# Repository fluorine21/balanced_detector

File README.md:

# balanced_detector
A balanced amplifier used to create a balanced photodetector out of two seperate photodetectors.

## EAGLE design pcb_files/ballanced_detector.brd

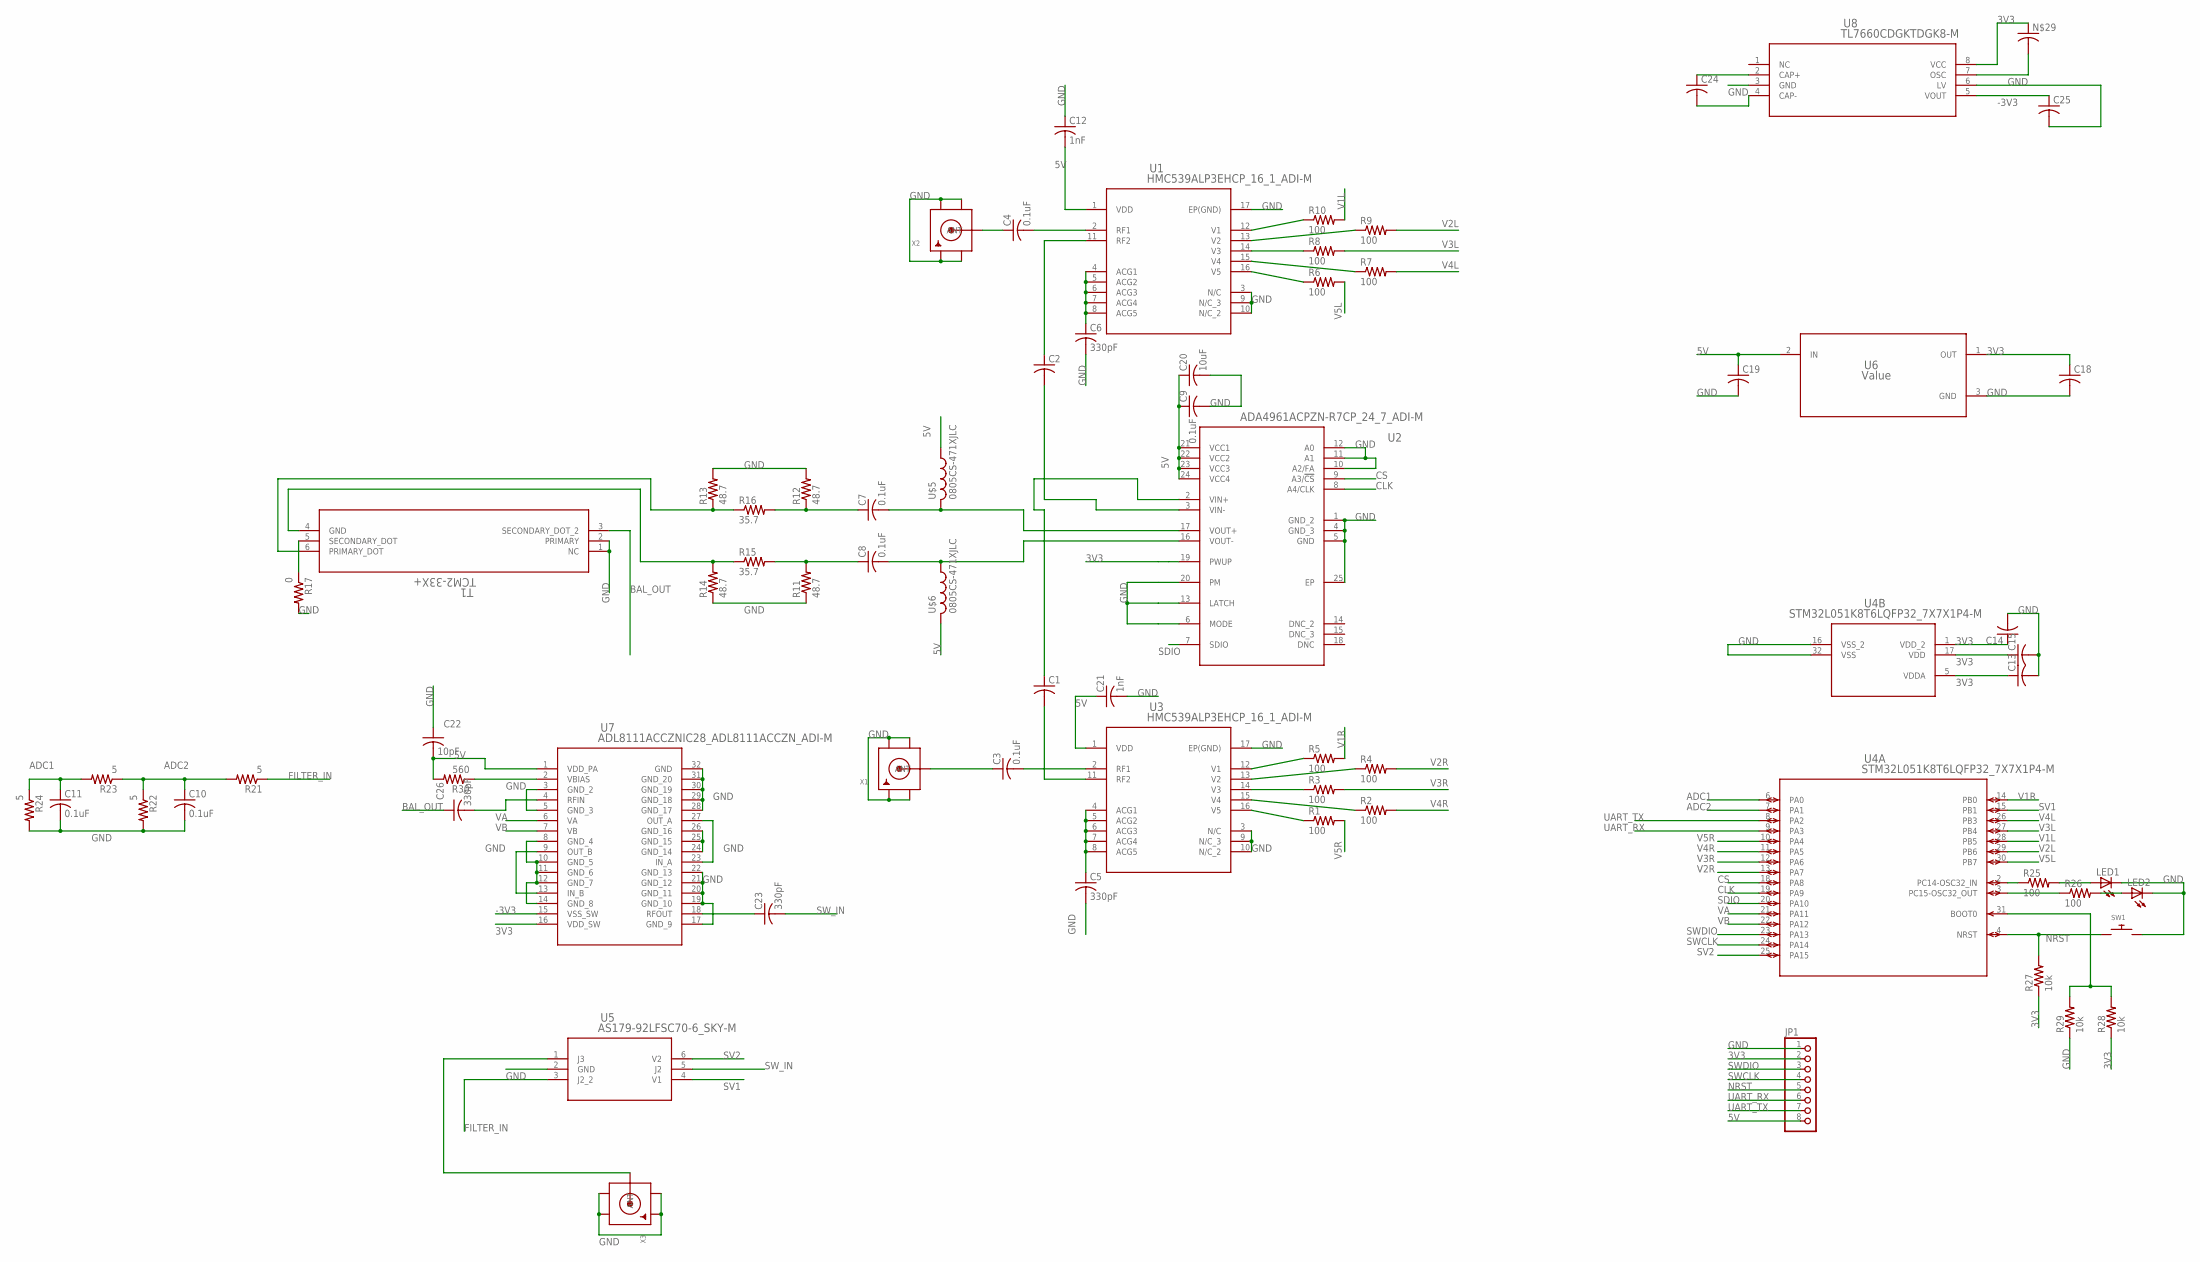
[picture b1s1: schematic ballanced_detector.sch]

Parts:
C1, C2, C13, C14, C15, C18, C19: C-USC0402; C0402
C3, C4, C7, C8, C9, C10, C11: 0.1uF; C0402
C5, C6, C23, C26: 330pF; C0402
C12, C21: 1nF; C0402
C20: 10uF; C0402
C22: 10pF; C0402
C24, C25: C-USC1210; C1210
JP1: PINHD-1X8CLEANBIG; 1X08-CLEANBIG
LED1, LED2: LEDCHIP-LED0805; CHIP-LED0805
N$29: C-USC1210; C1210
R1, R2, R3, R4, R5, R6, R7, R8, R9, R10, R25, R26: 100; R0402
R11, R12, R13, R14: 48.7; R0402
R15, R16: 35.7; R0402
R17: 0; R0402
R21, R22, R23, R24: 5; R0402
R27, R28, R29: 10k; R0402
R30: 560; R0402
SW1: SWITCH_PUSHBUTTONC&K_KSS; BTN_CK_KSS
T1: TCM2-33X+; DB1627_MNC
U1, U3: HMC539ALP3EHCP_16_1_ADI-M; HCP_16_1_ADI-M
U2: ADA4961ACPZN-R7CP_24_7_ADI-M; CP_24_7_ADI-M
U4: STM32L051K8T6LQFP32_7X7X1P4-M; LQFP32_7X7X1P4-M
U5: AS179-92LFSC70-6_SKY-M; SC70-6_SKY-M
U6: Value; DBZ0003A_N
U7: ADL8111ACCZNIC28_ADL8111ACCZN_ADI-M; IC28_ADL8111ACCZN_ADI-M
U8: TL7660CDGKTDGK8-M; DGK8-M
U$5, U$6: 0805CS-471XJLC; R0805
X1, X2, X3: SMACONNECTOR_EDGE; SMA_EDGELAUNCH

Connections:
3V3: C13.1, C14.1, C15.1, C18.1, JP1.2, N$29.1, R27.1, R28.1, U2.19 (PWUP), U4.1 (VDD_2), U4.5 (VDDA), U4.17 (VDD), U6.1 (OUT), U7.16 (VDD_SW), U8.8 (VCC)
5V: C9.1, C12.2, C19.1, C20.1, C21.1, C22.2, JP1.8, R30.2, U1.1 (VDD), U2.21 (VCC1), U2.22 (VCC2), U2.23 (VCC3), U2.24 (VCC4), U3.1 (VDD), U6.2 (IN), U7.1 (VDD_PA), U$5.1, U$6.2
-3V3: C25.1, U7.15 (VSS_SW), U8.5 (VOUT)
ADC1: C11.1, R23.2, R24.1, U4.6 (PA0)
ADC2: C10.1, R21.2, R22.1, R23.1, U4.7 (PA1)
BAL_OUT: C26.1, T1.3 (SECONDARY_DOT_2)
CLK: U2.8 (A4/CLK), U4.19 (PA9)
CS: U2.9 (A3/!CS), U4.18 (PA8)
FILTER_IN: R21.1, U5.3 (J2_2)
GND: C5.2, C6.2, C9.2, C10.2, C11.2, C12.1, C13.2, C14.2, C15.2, C18.2, C19.2, C20.2, C21.2, C22.1, C25.2, JP1.1, LED1.C, LED2.C, R11.1, R12.2, R13.2, R14.1, R17.2, R22.2, R24.2, R29.1, SW1.P$2, T1.1 (NC), T1.2 (PRIMARY), U1.3 (N/C), U1.9 (N/C_3), U1.10 (N/C_2), U1.17 (EP(GND)), U2.1 (GND_2), U2.4 (GND_3), U2.5 (GND), U2.6 (MODE), U2.10 (A2/FA), U2.11 (A1), U2.12 (A0), U2.13 (LATCH), U2.20 (PM), U2.25 (EP), U3.3 (N/C), U3.9 (N/C_3), U3.10 (N/C_2), U3.17 (EP(GND)), U4.16 (VSS_2), U4.32 (VSS), U5.2 (GND), U6.3 (GND), U7.3 (GND_2), U7.5 (GND_3), U7.8 (GND_4), U7.10 (GND_5), U7.11 (GND_6), U7.12 (GND_7), U7.14 (GND_8), U7.17 (GND_9), U7.19 (GND_10), U7.20 (GND_11), U7.21 (GND_12), U7.22 (GND_13), U7.24 (GND_14), U7.25 (GND_15), U7.26 (GND_16), U7.28 (GND_17), U7.29 (GND_18), U7.30 (GND_19), U7.31 (GND_20), U7.32 (GND), U8.3 (GND), U8.6 (LV), X1.GND@1 (GND4), X1.GND@2 (GND3), X1.GND@3 (GND2), X1.GND@4 (GND1), X2.GND@1 (GND4), X2.GND@2 (GND3), X2.GND@3 (GND2), X2.GND@4 (GND1), X3.GND@1 (GND4), X3.GND@2 (GND3), X3.GND@3 (GND2), X3.GND@4 (GND1)
unnamed: C1.2, U3.11 (RF2)
unnamed: C1.1, U2.2 (VIN+)
unnamed: C2.2, U2.3 (VIN-)
unnamed: C2.1, U1.11 (RF2)
unnamed: C3.2, U3.2 (RF1)
unnamed: C4.1, X2.P (ANT)
unnamed: C4.2, U1.2 (RF1)
unnamed: C3.1, X1.P (ANT)
unnamed: C7.2, U2.17 (VOUT+), U$5.2
unnamed: C8.2, U2.16 (VOUT-), U$6.1
unnamed: C8.1, R11.2, R15.2
unnamed: C5.1, U3.4 (ACG1), U3.5 (ACG2), U3.6 (ACG3), U3.7 (ACG4), U3.8 (ACG5)
unnamed: C6.1, U1.4 (ACG1), U1.5 (ACG2), U1.6 (ACG3), U1.7 (ACG4), U1.8 (ACG5)
unnamed: R10.1, U1.12 (V1)
unnamed: R9.1, U1.13 (V2)
unnamed: R8.1, U1.14 (V3)
unnamed: R7.1, U1.15 (V4)
unnamed: R6.1, U1.16 (V5)
unnamed: R5.1, U3.12 (V1)
unnamed: R4.1, U3.13 (V2)
unnamed: R3.1, U3.14 (V3)
unnamed: R2.1, U3.15 (V4)
unnamed: R1.1, U3.16 (V5)
unnamed: C7.1, R12.1, R16.2
unnamed: R14.2, R15.1, T1.4 (GND)
unnamed: R13.1, R16.1, T1.6 (PRIMARY_DOT)
unnamed: C26.2, U7.4 (RFIN)
unnamed: C23.1, U7.18 (RFOUT)
unnamed: N$29.2, U8.7 (OSC)
unnamed: C24.1, U8.2 (CAP+)
unnamed: U5.1 (J3), X3.P (ANT)
unnamed: R25.1, U4.2 (PC14-OSC32_IN)
unnamed: R26.1, U4.3 (PC15-OSC32_OUT)
unnamed: LED1.A, R25.2
unnamed: LED2.A, R26.2
unnamed: C24.2, U8.4 (CAP-)
unnamed: R28.2, R29.2, U4.31 (BOOT0)
unnamed: R17.1, T1.5 (SECONDARY_DOT)
unnamed: U7.23 (IN_A), U7.27 (OUT_A)
unnamed: U7.9 (OUT_B), U7.13 (IN_B)
unnamed: R30.1, U7.2 (VBIAS)
NRST: JP1.5, R27.2, SW1.P$1, U4.4 (NRST)
SDIO: U2.7 (SDIO), U4.20 (PA10)
SV1: U4.15 (PB1), U5.4 (V1)
SV2: U4.25 (PA15), U5.6 (V2)
SWCLK: JP1.4, U4.24 (PA14)
SWDIO: JP1.3, U4.23 (PA13)
SW_IN: C23.2, U5.5 (J2)
UART_RX: JP1.6, U4.9 (PA3)
UART_TX: JP1.7, U4.8 (PA2)
V1L: R10.2, U4.28 (PB5)
V1R: R5.2, U4.14 (PB0)
V2L: R9.2, U4.29 (PB6)
V2R: R4.2, U4.13 (PA7)
V3L: R8.2, U4.27 (PB4)
V3R: R3.2, U4.12 (PA6)
V4L: R7.2, U4.26 (PB3)
V4R: R2.2, U4.11 (PA5)
V5L: R6.2, U4.30 (PB7)
V5R: R1.2, U4.10 (PA4)
VA: U4.21 (PA11), U7.6 (VA)
VB: U4.22 (PA12), U7.7 (VB)

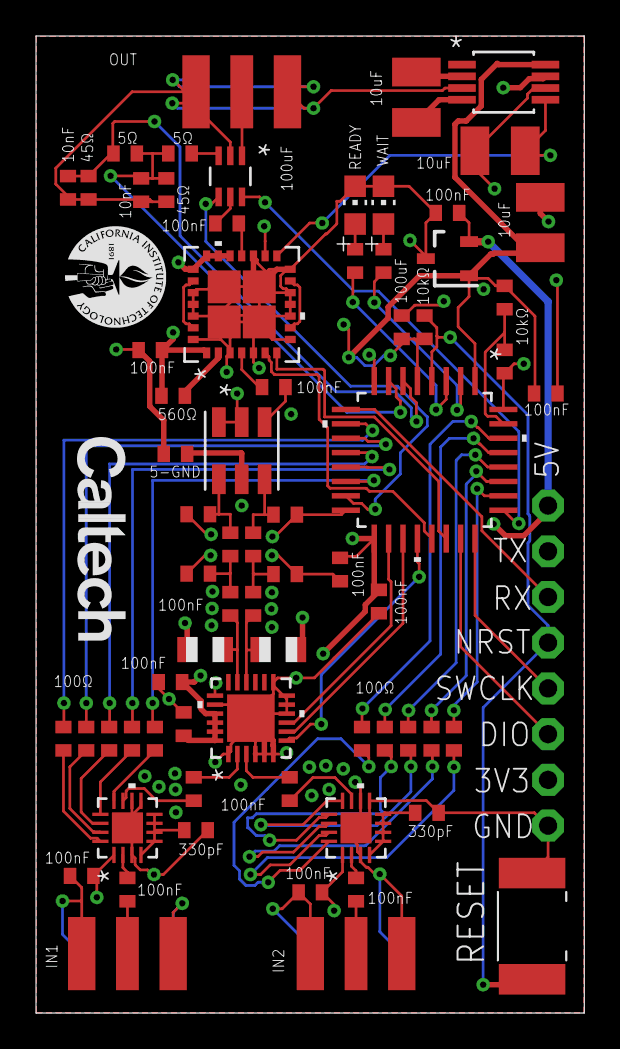
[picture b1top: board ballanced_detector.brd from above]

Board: 4 copper layers, 30.5 x 54.3 mm, 70 parts (0 on the bottom side), 72 nets.

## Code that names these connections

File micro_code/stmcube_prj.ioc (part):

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Mcu.Name=STM32L051K(6-8)Tx
Mcu.Package=LQFP32
Mcu.UserName=STM32L051K8Tx
PA0.GPIOParameters=GPIO_Label
PA0.GPIO_Label=ADC1
PA0.Mode=IN0
PA0.Signal=ADC_IN0
PA1.GPIOParameters=GPIO_Label
PA1.GPIO_Label=ADC2
PA1.Mode=IN1
PA1.Signal=ADC_IN1
PA10.GPIOParameters=GPIO_Label
PA10.GPIO_Label=SDIO
PA10.Signal=GPIO_Output
PA11.GPIOParameters=GPIO_Label
PA11.GPIO_Label=VA
PA11.Signal=GPIO_Output
PA12.GPIOParameters=GPIO_Label
PA12.GPIO_Label=VB
PA12.Signal=GPIO_Output
PA13.Mode=Serial_Wire
PA13.Signal=SYS_SWDIO
PA14.Mode=Serial_Wire
PA14.Signal=SYS_SWCLK
PA15.GPIOParameters=GPIO_Label
PA15.GPIO_Label=SV2
PA15.Signal=GPIO_Output
PA2.Mode=Asynchronous
PA2.Signal=USART2_TX
PA3.Mode=Asynchronous
PA3.Signal=USART2_RX
PA4.GPIOParameters=GPIO_Label
PA4.GPIO_Label=V5R
PA4.Signal=GPIO_Output
PA5.GPIOParameters=GPIO_Label
PA5.GPIO_Label=V4R
PA5.Signal=GPIO_Output
PA6.GPIOParameters=GPIO_Label
PA6.GPIO_Label=V3R
PA6.Signal=GPIO_Output
PA7.GPIOParameters=GPIO_Label
PA7.GPIO_Label=V2R
PA7.Signal=GPIO_Output
PA8.GPIOParameters=GPIO_Label
PA8.GPIO_Label=CS
PA8.Signal=GPIO_Output
PA9.GPIOParameters=GPIO_Label
PA9.GPIO_Label=SCLK
PA9.Signal=GPIO_Output
PB0.GPIOParameters=GPIO_Label
PB0.GPIO_Label=V1R
PB0.Signal=GPIO_Output
PB1.GPIOParameters=GPIO_Label
PB1.GPIO_Label=SV1
PB1.Signal=GPIO_Output
PB3.GPIOParameters=GPIO_Label
PB3.GPIO_Label=V4L
PB3.Signal=GPIO_Output
PB4.GPIOParameters=GPIO_Label
PB4.GPIO_Label=V3L
PB4.Signal=GPIO_Output
PB5.GPIOParameters=GPIO_Label
PB5.GPIO_Label=V1L
PB5.Signal=GPIO_Output
PB6.GPIOParameters=GPIO_Label
PB6.GPIO_Label=V2L
PB6.Signal=GPIO_Output
PB7.GPIOParameters=GPIO_Label
PB7.GPIO_Label=V5L
PB7.Signal=GPIO_Output
PC14-OSC32_IN.GPIOParameters=GPIO_Label
PC14-OSC32_IN.GPIO_Label=LED1
PC14-OSC32_IN.Signal=GPIO_Output
PC15-OSC32_OUT.GPIOParameters=GPIO_Label
PC15-OSC32_OUT.GPIO_Label=LED2
PC15-OSC32_OUT.Signal=GPIO_Output
RCC.SYSCLKFreq_VALUE=16000000
RCC.SYSCLKSource=RCC_SYSCLKSOURCE_HSI
board=custom

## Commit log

2021-06-29 implemented rest of functions over uart
2021-06-30 Fixed TrueStudio path issues and wrote part of interrupt initialization
2021-07-10 Changed driver to use FSM and interrupts
2021-07-23 Working interrupt driver with 16MHz clock
2021-08-07 push before reboot
2021-08-30 Made some small changes to the code
2021-10-31 push from tab
2021-11-29 Pushing with new sim files
2022-04-14 Started work on V2, schematic half way done
2022-04-21 Finished schematic, pushing before annotation
2022-04-21 Started working on PCB, fixed some footprint import issues
2022-04-25 Did more routing
2022-04-26 Nearly done with routing
2022-04-26 Fixed footprint for SMA connector and finished up rest of routing
2022-04-26 Board nearly done, just need to do final DRC on schematic and pcb

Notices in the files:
parts and their libraries:
COPYRIGHT: Copyright (C) 2018 Accelerated Designs. All rights reserved
COPYRIGHT: Copyright (C) 2016 Accelerated Designs. All rights reserved
